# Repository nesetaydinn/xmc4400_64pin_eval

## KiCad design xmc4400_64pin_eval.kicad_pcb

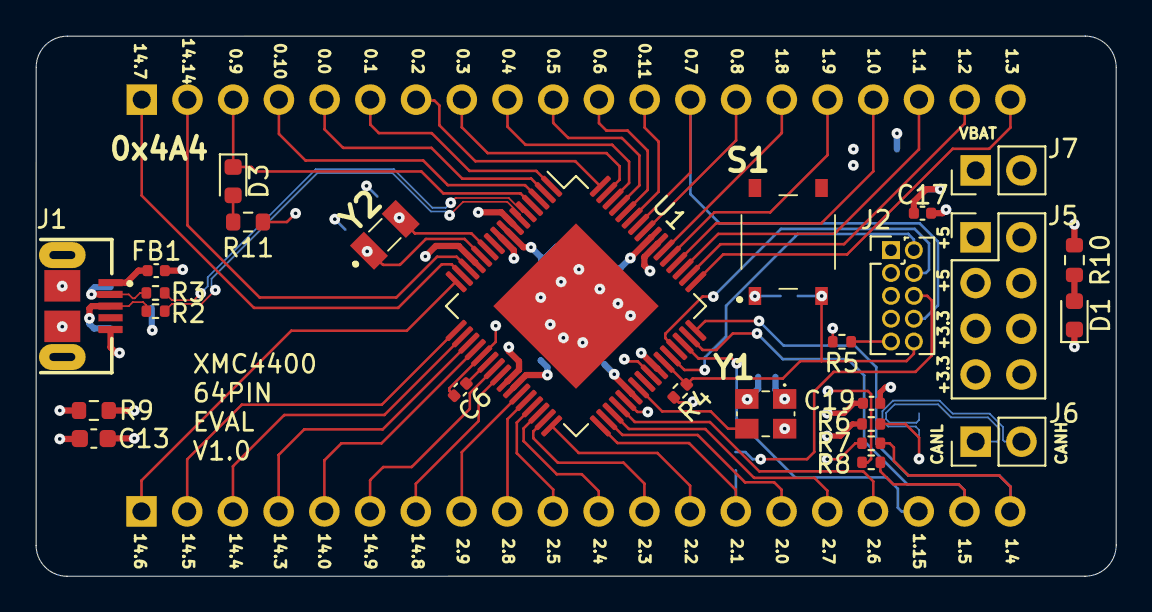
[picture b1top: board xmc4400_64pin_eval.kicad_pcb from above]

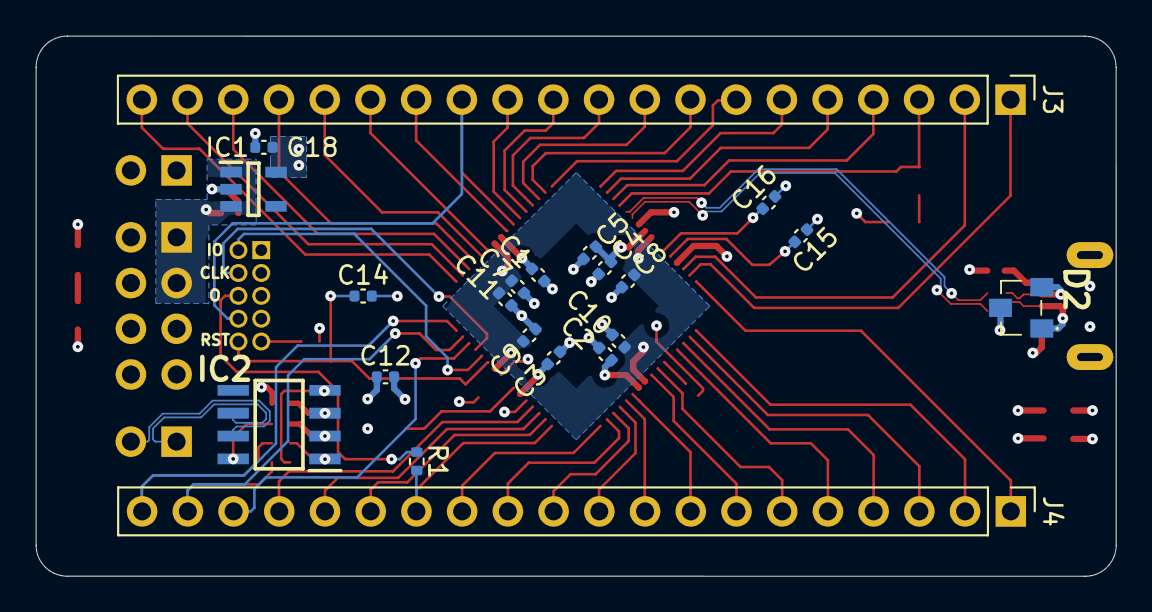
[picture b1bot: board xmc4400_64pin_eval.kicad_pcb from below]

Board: 4 copper layers, 60.0 x 30.0 mm, 47 parts (21 on the bottom side), 68 nets.

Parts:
C1, C2, C3, C4, C6, C7, C8, C9, C10, C12, C19: 100nF; C_0402_1005Metric
C5: 10uF; C_0402_1005Metric
C11: 4.7uF; C_0402_1005Metric
C13: 100nF; C_0603_1608Metric
C14: 10nF; C_0402_1005Metric
C15, C16: 15pF; C_0402_1005Metric
C17, C18: 1uF; C_0402_1005Metric
D1: Pow; LED_0603_1608Metric
D2: PGB102ST23WRHF
D3: USR; LED_0603_1608Metric
FB1: BLM15PD600SN1D; C_0402_1005Metric
IC1: TLV75533PDBVR; SOT95P280X145-5N
IC2: SN65HVD230DR; SOT127P600X175-8N
J1: VCP; GCT_USB3080-XX-00-A_REVE
J2: SWD & JTAG; PinHeader_2x05_P1.27mm_Vertical
J3: IO_1; PinHeader_1x20_P2.54mm_Vertical
J4: IO_2; PinHeader_1x20_P2.54mm_Vertical
J5: POW; PinHeader_2x04_P2.54mm_Vertical
J6: CAN; PinHeader_1x02_P2.54mm_Vertical
J7: Vbat; PinHeader_1x02_P2.54mm_Vertical
R1, R5, R7, R8: 0R; R_0402_1005Metric
R2, R3: 22R; R_0402_1005Metric
R4, R6: 10kR; R_0402_1005Metric
R9: 1MR; R_0603_1608Metric
R10, R11: 150R; R_0603_1608Metric
S1: Reset; PTS526SM15SMTR2LFS
U1: XMC440x-LQFP64; LQFP-64-1EP_10x10mm_P0.5mm_EP6.5x6.5mm
Y1: ASE-12.000MHZ-LC-T; ASE24576MHZLCT
Y2: 32.768kHz; ABS0716632768KHZT

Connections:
+5V: C17.2, IC1.1 (IN), IC1.3 (EN), J5.1, J5.3
+XMC_VBAT: J7.1, U1.13 (VBAT)
/VCP_D+: D2.1, J1.3 (D+), R2.2
/VCP_D-: D2.2, J1.2 (D-), R3.2
GND: C1.2, C2.2, C3.2, C4.2, C5.2, C6.2, C7.2, C8.2, C9.2, C10.2, C11.2, C12.2, C13.1, C14.2, C15.2, C16.2, C17.1, C18.1, C19.2, D1.1 (K), D2.3, IC1.2 (GND), IC2.2 (GND), J1.5 (GND), J2.3, J2.5, J5.2, J5.4, J5.6, J5.8, J7.2, R5.2, R6.1, R9.1, S1.1, U1.21 (VAGND), U1.37 (VSS), U1.41 (VSSO), U1.65 (EP), Y1.2 (GND/CASE)
GNDA: C13.2, J1.6 (SHIELD), J1.7 (SHIELD), J1.8 (SHIELD), J1.9 (SHIELD), R9.2
IC_CAN_+: IC2.7 (CANH), J6.2
IC_CAN_-: IC2.6 (CANL), J6.1
unnamed: D1.2 (A), R10.2
unnamed: D3.2 (A), R11.2
unnamed: IC2.8 (RS), R6.2
unnamed: FB1.2, J1.1 (VBUS)
unnamed: J2.9, R5.1
unnamed: C6.1, U1.22 (VAREF)
P0_0: J3.5, U1.2 (P0.0)
P0_1: J3.6, U1.1 (P0.1)
P0_2: J3.7, U1.64 (P0.2)
P0_3: J3.8, U1.63 (P0.3)
P0_4: J3.9, U1.62 (P0.4)
P0_5: J3.10, U1.61 (P0.5)
P0_6: J3.11, U1.60 (P0.6)
P0_7: J2.8, J3.13, U1.58 (P0.7)
P0_8: J3.14, U1.57 (P0.8)
P0_9: D3.1 (K), J3.3, U1.4 (P0.9)
P0_10: J3.4, U1.3 (P0.10)
P0_11: J3.12, U1.59 (P0.11)
P1_0: J3.17, U1.52 (P1.0)
P1_1: J3.18, U1.51 (P1.1)
P1_2: J3.19, U1.50 (P1.2)
P1_3: J3.20, U1.49 (P1.3)
P1_4: J4.20, R7.2, U1.48 (P1.4)
P1_5: J4.19, R8.2, U1.47 (P1.5)
P1_8: J3.15, U1.54 (P1.8)
P1_9: J3.16, U1.53 (P1.9)
P1_15: J4.18, U1.46 (P1.15)
P2_0: J4.15, U1.34 (P2.0)
P2_1: J4.14, R1.2, U1.33 (P2.1)
P2_2: J4.13, U1.32 (P2.2)
P2_3: J4.12, U1.31 (P2.3)
P2_4: J4.11, U1.30 (P2.4)
P2_5: J4.10, U1.29 (P2.5)
P2_6: J4.17, U1.36 (P2.6)
P2_7: J4.16, U1.35 (P2.7)
P2_8: J4.9, U1.28 (P2.8)
P2_9: J4.8, U1.27 (P2.9)
P14_0: J4.5, U1.20 (P14.0)
P14_3: J4.4, U1.19 (P14.3)
P14_4: J4.3, U1.18 (P14.4)
P14_5: J4.2, U1.17 (P14.5)
P14_6: J4.1, U1.16 (P14.6)
P14_7: J3.1, U1.15 (P14.7)
P14_8: J4.7, U1.24 (P14.8)
P14_9: J4.6, U1.23 (P14.9)
P14_14: J3.2, U1.14 (P14.14)
SWDO_P2.1: J2.6, R1.1
VBUS: FB1.1, U1.7 (VBUS)
XMC_CAN_RX: IC2.4 (R), R8.1
XMC_CAN_TX: IC2.1 (D), R7.1
XMC_RESET: C14.1, J2.10, R4.2, S1.3, U1.43 (PORST)
XMC_RTC_XTAL1: C16.1, U1.11 (RTC_XTAL1), Y2.2
XMC_RTC_XTAL2: C15.1, U1.12 (RTC_XTAL2), Y2.1
XMC_TCK/SWCLK: J2.4, U1.45 (TCK/SWCLK)
XMC_TMS/SWDIO: J2.2, U1.44 (TMS/SWDIO)
XMC_USB_D+: R2.1, U1.6 (USB_DP)
XMC_USB_D-: R3.1, U1.5 (USB_DM)
XMC_VDDC: C7.1, C8.1, C9.1, C10.1, C11.1, U1.9 (VDDC), U1.25 (VDDC), U1.42 (VDDC), U1.55 (VDDC)
XMC_VDDP: C1.1, C2.1, C3.1, C4.1, C5.1, C12.1, C18.2, C19.1, IC1.5 (OUT), IC2.3 (VCC), J2.1, J5.5, J5.7, R4.1, R10.1, R11.1, U1.8 (VDDP), U1.26 (VDDP), U1.38 (VDDP), U1.56 (VDDP), Y1.1 (TRI-STATE_(STBY)), Y1.4 (VDD)
XMC_XTAL1: U1.39 (XTAL1), Y1.3 (OUTPUT)

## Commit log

2023-03-24 Add pcb schematic and layout
2023-03-24 Add pics and sch's pdf
2023-05-03 Fix swd pins
